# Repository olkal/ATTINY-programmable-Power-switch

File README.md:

# ATTINY Power switch
This programmable MOSFET high side on/off power switch is based on the ATTINY85 chip and is intended for battery powered devices.

- 2-3 Lipo cells 
- Max operating voltage 16.0V (18V never exceed)
- Max current: needs to be tested, but up to 5A should be safe. See MOSFET data sheet for info.
- Power consumption in "off" mode with BOD disabled: 3uA
- Power consumption in "off" mode with BOD enabled: 20uA

### Configurable features in config.h file:
- LED behaviour
- Low battery voltage threshold, LED warning
- Very low battery voltage threshold, power off
- Button press and hold for a set time for power on
- Button press and hold for set time for power off
- Timer, delayed power off
- Timer, after power has been on for set time, switch power off
- PB3 pin signal (to for example a Raspberry Pi) initiating controlled shut-down, then switch the power off after a set time delay
-  +lots of other possibilities...

### Battery/voltage features using button switch:
- Auto calibrating internal voltmeter
- Auto set number of cells

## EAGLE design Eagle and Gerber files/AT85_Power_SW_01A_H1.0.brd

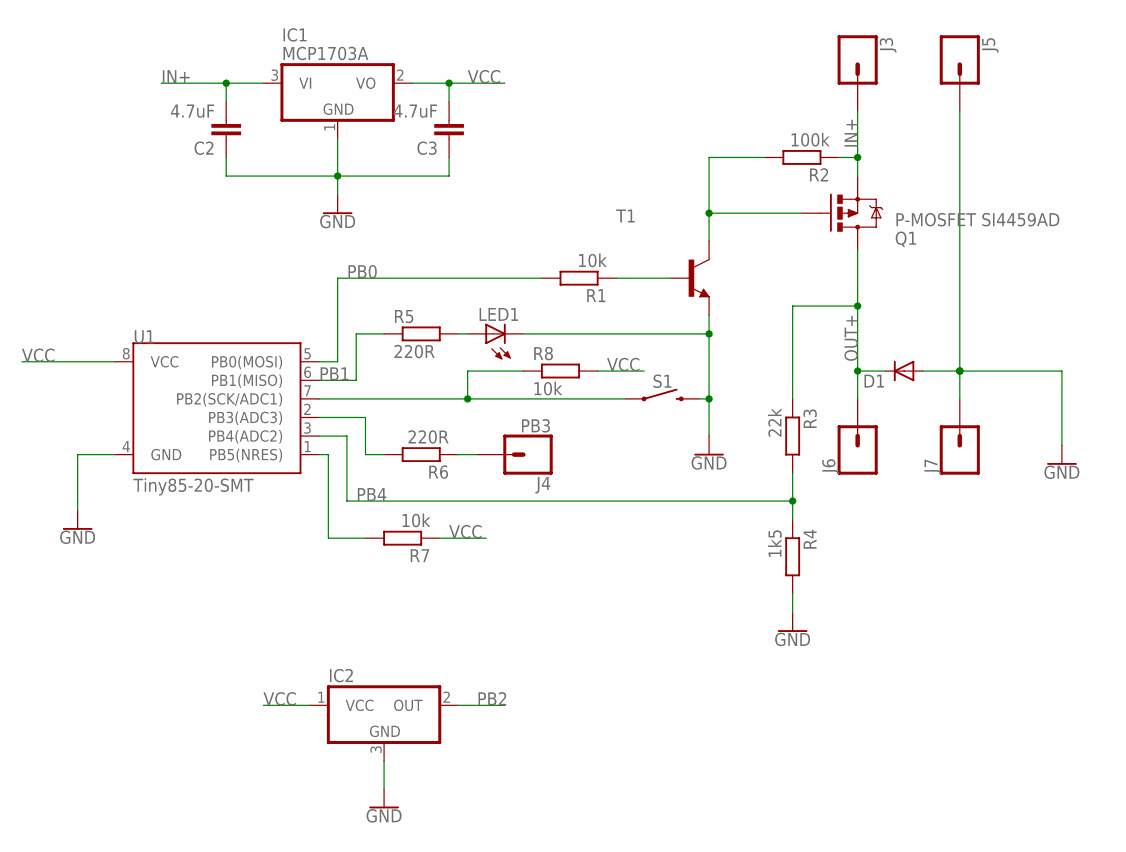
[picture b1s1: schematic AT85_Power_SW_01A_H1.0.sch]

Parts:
C2, C3: 4.7uF; C0805
D1: DIODE-DO-214AC; DO-214AC
IC1: MCP1703A; SOT23
IC2: SL353; SOT23
J3, J5, J6, J7: CONN_01PTH_LONGPAD; 1X01_LONGPAD
J4: PB3; 1X01
LED1: LED3MM
Q1: P-MOSFET SI4459AD; SO08
R1, R7, R8: 10k; R0805
R2: 100k; R0805
R3: 22k; R0805
R4: 1k5; R0805
R5, R6: 220R; R0805
S1: TACTILE_SWITCH_SMD_6.2MM_TALL
T1: MMBT2222ALT1-NPN-SOT23-BEC; SOT23-BEC
U1: Tiny85-20-SMT; SO08-EIAJ_MCU

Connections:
GATE: Q1.4 (G), R2.2, T1.C
GND: C2.1, C3.1, D1.A, IC1.1 (GND), IC2.3 (GND), J5.1, J7.1, LED1.K (C), R4.2, S1.B2 (2), T1.E, U1.4 (GND)
IN+: C2.2, IC1.3 (VI), J3.1, Q1.1 (S), Q1.2 (S), Q1.3 (S), R2.1
unnamed: LED1.A, R5.2
unnamed: R1.1, T1.B
OUT+: D1.C, J6.1, Q1.5 (D), Q1.6 (D), Q1.7 (D), Q1.8 (D), R3.1
PB0: R1.2, U1.5 (PB0(MOSI))
PB1: R5.1, U1.6 (PB1(MISO))
PB2: IC2.2 (OUT), R8.1, S1.A2 (1), U1.7 (PB2(SCK/ADC1))
PB3: R6.2, U1.2 (PB3(ADC3))
PB3_: J4.1, R6.1
PB4: R3.2, R4.1, U1.3 (PB4(ADC2))
RST: R7.2, U1.1 (PB5(NRES))
VCC: C3.2, IC1.2 (VO), IC2.1 (VCC), R7.1, R8.2, U1.8 (VCC)

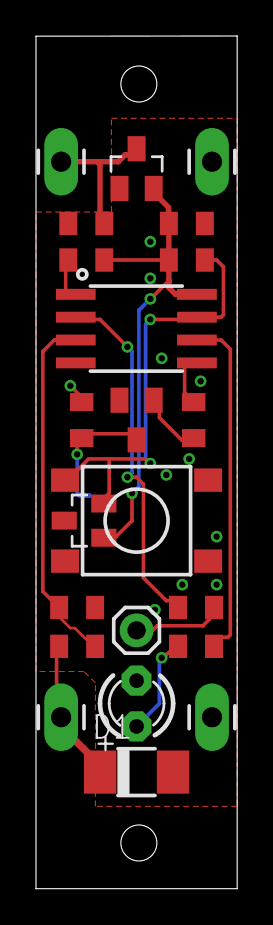
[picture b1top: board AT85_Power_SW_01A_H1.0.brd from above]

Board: 2 copper layers, 11.2 x 47.4 mm, 23 parts (1 on the bottom side), 14 nets.

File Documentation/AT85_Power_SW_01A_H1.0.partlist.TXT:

Partlist

Exported from AT85_Power_SW_01A_H1.0.sch at 14.06.2018 19.48

EAGLE Version 8.2.1 Copyright (c) 1988-2017 Autodesk, Inc.

Assembly variant: 

Part     Value             Device                               Package                       Library             Sheet

C2       4.7uF/25V         CAP_SMD_C0805                        C0805                         OKA-Cap-Resistor    1 
C3       4.7uF/25V         CAP_SMD_C0805                        C0805                         OKA-Cap-Resistor    1
D1                         DIODE-DO-214AC                       DO-214AC                      diode               1 -> Otional diode for inductive loads
IC1      MCP1703A          MCP1703CB                            SOT23                         linear              1
IC2      SL353             SL353                                SOT23                         OKA-IC              1 -> Otional hall sensor
LED1                       LED3MM                               LED3MM                        adafruit            1
Q1       P-MOSFET SI4459AD MOSFET-PCHANNEL                      SO08                          User-Submitted      1
R1       10k               RESISTOR_SMDR0805                    R0805                         OKA-Cap-Resistor    1
R2       100k              RESISTOR_SMDR0805                    R0805                         OKA-Cap-Resistor    1
R3       22k               RESISTOR_SMDR0805                    R0805                         OKA-Cap-Resistor    1
R4       1k5               RESISTOR_SMDR0805                    R0805                         OKA-Cap-Resistor    1
R5       220R              RESISTOR_SMDR0805                    R0805                         OKA-Cap-Resistor    1
R6       220R              RESISTOR_SMDR0805                    R0805                         OKA-Cap-Resistor    1
R7       10k               RESISTOR_SMDR0805                    R0805                         OKA-Cap-Resistor    1
R8       10k               RESISTOR_SMDR0805                    R0805                         OKA-Cap-Resistor    1
S1                         MOMENTARY-SWITCH-SPST-SMD-6.2MM-TALL TACTILE_SWITCH_SMD_6.2MM_TALL SparkFun-Switches   1
T1       2N2222            MMBT2222ALT1-NPN-SOT23-BEC           SOT23-BEC                     transistor          1
U1       Tiny85-20-SMT     ATTINY45TINY85-20-SMT                SO08-EIAJ_MCU                 SparkFun-Retired    1

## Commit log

2018-06-15 upload
2018-06-16 license

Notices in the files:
parts and their libraries:
User-Submitted: Licensing: Creative Commons ShareAlike 4.0 International - https://creativecommons.org/licenses/by-sa/4.0
